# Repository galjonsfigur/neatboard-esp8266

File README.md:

# ESP8266 NeatBoard

Small clone of WeMos D1 Mini couple additional functionalities:
- Pin-out and footprint compatible with WeMos D1 Mini (exception: board outline)
- Additional jumpers for Deep Sleep and disabling LEDs
- CP2102 USB-UART bridge (no more problems with CH340)
- UART activity LED
- DC/DC instead of LDO for better efficiency
- Bigger PCB antenna, based on DN007 document from Texas Instruments
- Integrated Fuse and ESD protection

Board was tested on 1.0mm 2-layer stackup. Matching was not verified with VNA. Components used to built couple units were taken from ESP-01 boards, so there is possibility to use other values (LEDs, SPI Flash etc.)

Gerber files (both old, tested version and new, regenerated in KiCad 8), Schematic and Interactive BOM (missing MPNs) are present in `production-files` folder.

After assembly, board should work without any additional steps, just like D1 mini or similar. 

## License
MIT

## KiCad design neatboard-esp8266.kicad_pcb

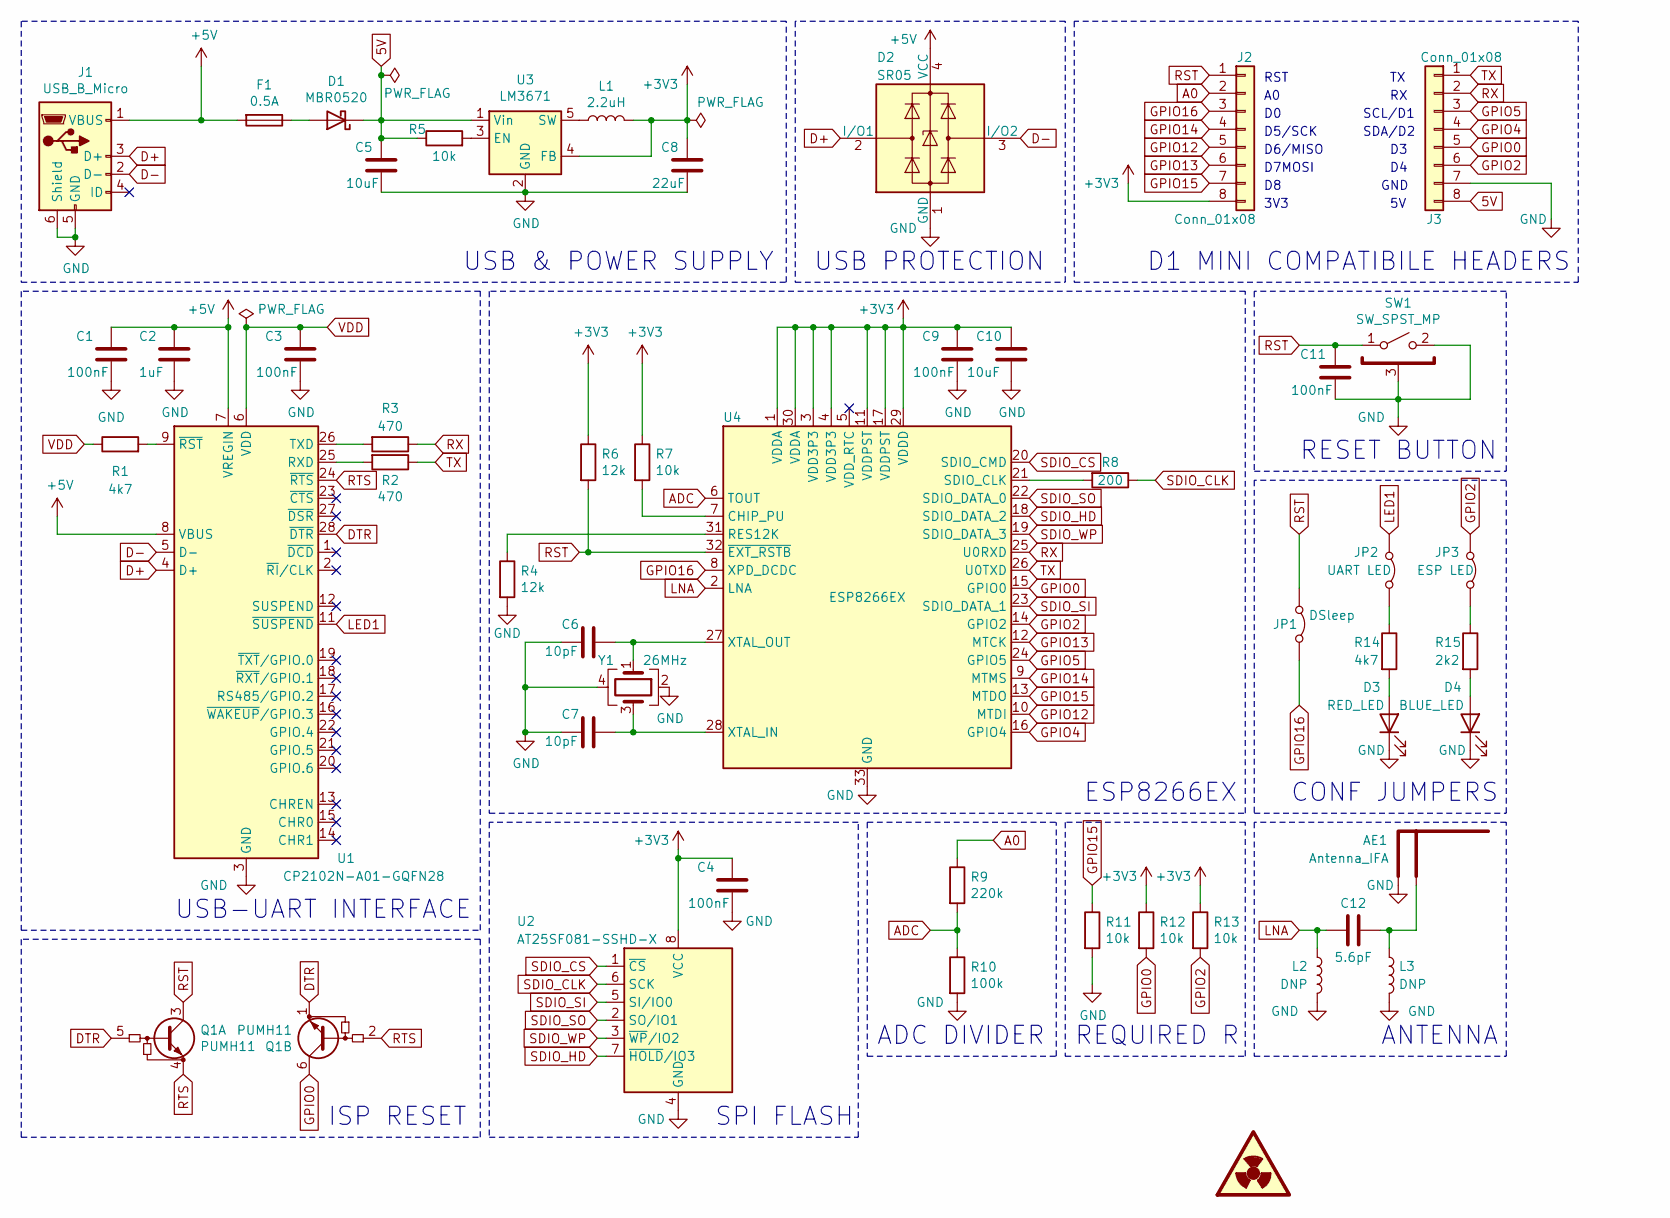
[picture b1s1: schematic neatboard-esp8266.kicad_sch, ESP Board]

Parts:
AE1: Antenna_IFA; TI_DN007_2.4GHz
C1, C3, C4, C9, C11: 100nF; C_0402_1005Metric
C2: 1uF; C_0603_1608Metric
C5: 10uF; C_0805_2012Metric
C6, C7: 10pF; C_0402_1005Metric
C8: 22uF; C_0805_2012Metric
C10: 10uF; C_0603_1608Metric
C12: 5.6pF; C_0402_1005Metric
D1: MBR0520; D_SOD-123
D2: SR05; SOT-143
D3: RED_LED; LED_0402_1005Metric
D4: BLUE_LED; LED_0402_1005Metric
F1: 0.5A; Fuse_0402_1005Metric
J1: USB_B_Micro; USB_Micro-B_Unknown_5s_SMT
J2, J3: Conn_01x08; PinHeader_1x08_P2.54mm_Vertical
JP1: DSleep; SolderJumper-2_P1.3mm_Open_RoundedPad1.0x1.5mm
JP2: UART LED; SolderJumper-2_P1.3mm_Bridged_RoundedPad1.0x1.5mm
JP3: ESP LED; SolderJumper-2_P1.3mm_Bridged_RoundedPad1.0x1.5mm
L1: 2.2uH; L_Sunlord-SWPA3010S
L2, L3: DNP; L_0402_1005Metric
LG1: LOGO; Galion_Logo_Small
Q1: PUMH11; SOT-363_SC-70-6
R1, R14: 4k7; R_0402_1005Metric
R2, R3: 470; R_0402_1005Metric
R4, R6: 12k; R_0402_1005Metric
R5, R7, R11, R12, R13: 10k; R_0402_1005Metric
R8: 200; R_0402_1005Metric
R9: 220k; R_0402_1005Metric
R10: 100k; R_0402_1005Metric
R15: 2k2; R_0402_1005Metric
SW1: SW_SPST_MP; SW_SPST_1TS003B
U1: CP2102N-A01-GQFN28; QFN-28-1EP_5x5mm_P0.5mm_EP3.35x3.35mm
U2: AT25SF081-SSHD-X; SOIC-8_3.9x4.9mm_P1.27mm
U3: LM3671; TSOT-23-5
U4: ESP8266EX; QFN-32-1EP_5x5mm_P0.5mm_EP3.45x3.45mm
Y1: 26MHz; Crystal_SMD_3225-4Pin_3.2x2.5mm

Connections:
5V: C5.1, D1.1 (K), J3.8, R5.1, U3.1 (Vin)
+3V3: C4.1, C8.1, C9.1, C10.1, J2.8, L1.2, R6.1, R7.1, R12.1, R13.1, U2.8 (VCC), U3.4 (FB), U4.1 (VDDA), U4.3 (VDD3P3), U4.4 (VDD3P3), U4.11 (VDDPST), U4.17 (VDDPST), U4.29 (VDDD), U4.30 (VDDA)
+5V: C1.1, C2.1, D2.4 (VCC), F1.2, J1.1 (VBUS), U1.7 (VREGIN), U1.8 (VBUS)
A0: J2.2, R9.1
ADC: R9.2, R10.1, U4.6 (TOUT)
D+: D2.2 (I/O1), J1.3 (D+), U1.4 (D+)
D-: D2.3 (I/O2), J1.2 (D-), U1.5 (D-)
DTR: Q1.1 (E2), Q1.5 (B1), U1.28 (~DTR)
GND: AE1.1 (GND), C1.2, C2.2, C3.2, C4.2, C5.2, C6.2, C7.2, C8.2, C9.2, C10.2, C11.2, D2.1 (GND), D3.1 (K), D4.1 (K), J1.5 (GND), J1.6 (Shield), J3.7, L2.2, L3.2, R4.2, R10.2, R11.2, SW1.2 (B), SW1.3 (MP), U1.3 (GND), U1.29 (GND), U2.4 (GND), U3.2 (GND), U4.33 (GND), Y1.2, Y1.4
GPIO0: J3.5, Q1.6 (C2), R12.2, U4.15 (GPIO0)
GPIO2: J3.6, JP3.1 (A), R13.2, U4.14 (GPIO2)
GPIO4: J3.4, U4.16 (GPIO4)
GPIO5: J3.3, U4.24 (GPIO5)
GPIO12: J2.5, U4.10 (MTDI)
GPIO13: J2.6, U4.12 (MTCK)
GPIO14: J2.4, U4.9 (MTMS)
GPIO15: J2.7, R11.1, U4.13 (MTDO)
GPIO16: J2.3, JP1.2 (B), U4.8 (XPD_DCDC)
LED1: JP2.1 (A), U1.11 (~SUSPEND)
LNA: C12.2, L2.1, U4.2 (LNA)
unnamed: AE1.2 (FEED), C12.1, L3.1
unnamed: D1.2 (A), F1.1
unnamed: D3.2 (A), R14.2
unnamed: D4.2 (A), R15.2
unnamed: JP2.2 (B), R14.1
unnamed: JP3.2 (B), R15.1
unnamed: R2.2, U1.25 (RXD)
unnamed: R3.2, U1.26 (TXD)
unnamed: R1.2, U1.9 (~RST)
unnamed: R5.2, U3.3 (EN)
unnamed: L1.1, U3.5 (SW)
unnamed: R7.2, U4.7 (CHIP_PU)
unnamed: R4.1, U4.31 (RES12K)
unnamed: R8.2, U4.21 (SDIO_CLK)
unnamed: C7.1, U4.28 (XTAL_IN), Y1.3
unnamed: C6.1, U4.27 (XTAL_OUT), Y1.1
RST: C11.1, J2.1, JP1.1 (A), Q1.3 (C1), R6.2, SW1.1 (A), U4.32 (~EXT_RSTB)
RTS: Q1.2 (B2), Q1.4 (E1), U1.24 (~RTS)
RX: J3.2, R3.1, U4.25 (U0RXD)
SDIO_CLK: R8.1, U2.6 (SCK)
SDIO_CS: U2.1 (~CS), U4.20 (SDIO_CMD)
SDIO_HD: U2.7 (~HOLD/IO3), U4.18 (SDIO_DATA_2)
SDIO_SI: U2.5 (SI/IO0), U4.23 (SDIO_DATA_1)
SDIO_SO: U2.2 (SO/IO1), U4.22 (SDIO_DATA_0)
SDIO_WP: U2.3 (~WP/IO2), U4.19 (SDIO_DATA_3)
TX: J3.1, R2.1, U4.26 (U0TXD)
VDD: C3.1, R1.1, U1.6 (VDD)

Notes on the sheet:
ADC DIVIDER
RST
SCL/D1
ISP RESET
CONF JUMPERS
SPI FLASH
USB PROTECTION
USB & POWER SUPPLY
USB-UART INTERFACE
D7MOSI
D6/MISO
ESP8266EX
ANTENNA
D5/SCK
D1 MINI COMPATIBILE HEADERS
3V3
SDA/D2
GND
REQUIRED R
RESET BUTTON

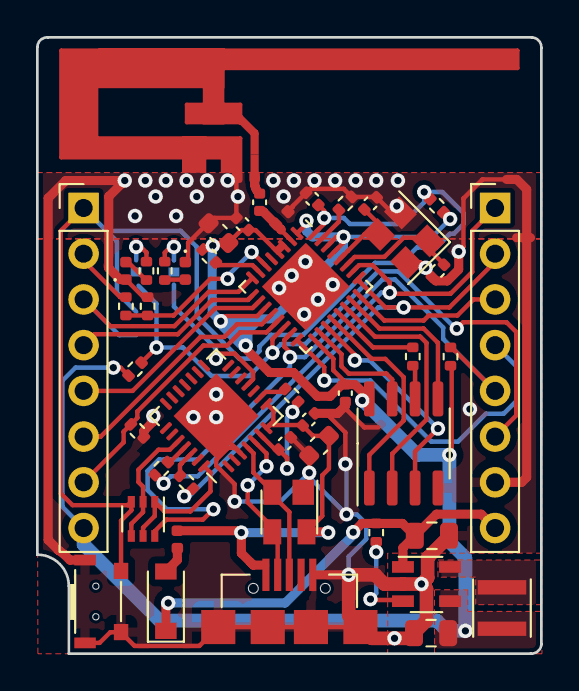
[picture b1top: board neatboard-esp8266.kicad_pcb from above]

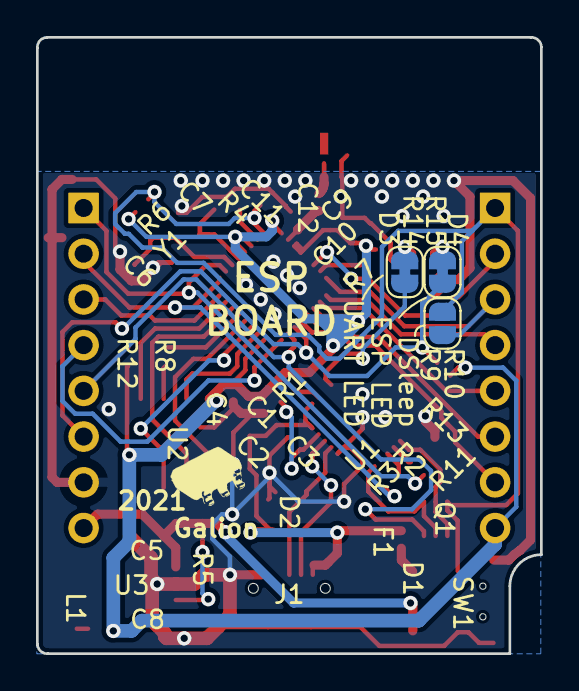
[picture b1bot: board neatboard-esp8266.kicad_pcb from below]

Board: 2 copper layers, 28.0 x 34.2 mm, 50 parts (4 on the bottom side), 47 nets.

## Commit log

2024-10-08 First and probably the only commit.
